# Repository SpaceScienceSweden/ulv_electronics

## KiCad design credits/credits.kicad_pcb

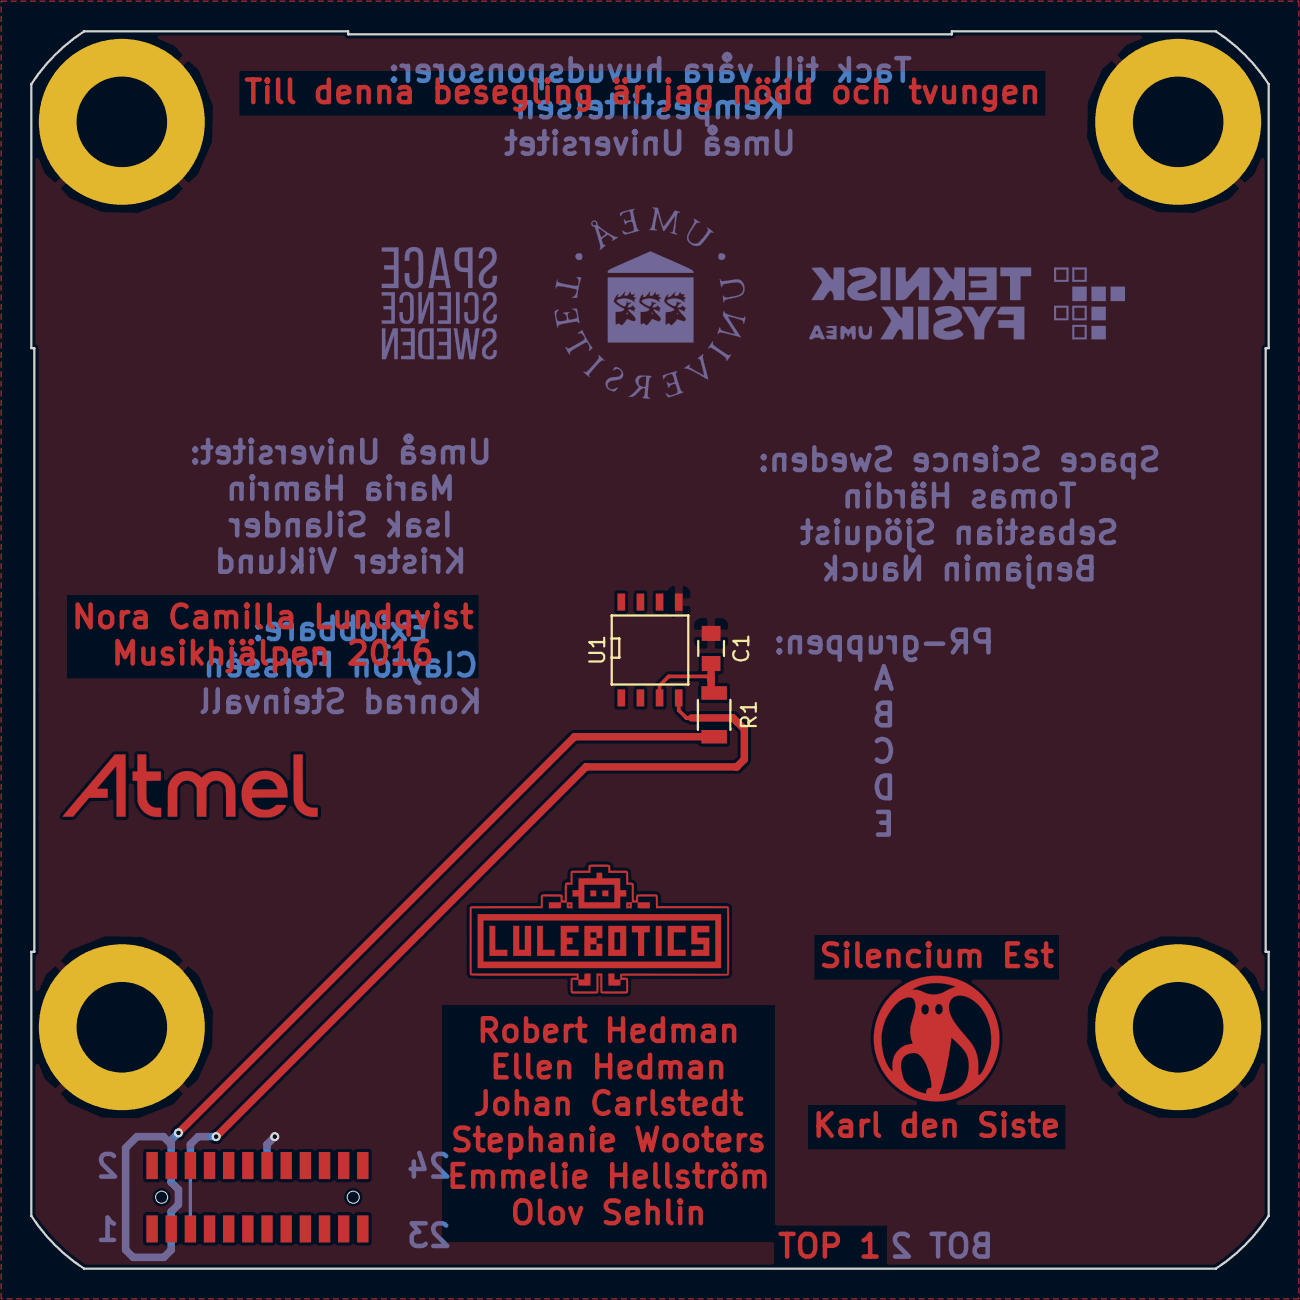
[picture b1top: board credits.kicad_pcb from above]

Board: 2 copper layers, 82.0 x 82.0 mm, 8 parts (1 on the bottom side), 4 nets.

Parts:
C1: 100n; C_0805
P1: CONN_02X12; LPPB122NFSP-RC-backpads-mirrored
P8, P9, P10, P11: M6; M6_PTH
R1: 0; R_1206
U1: DS18B20Z; SOIC-8-N

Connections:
+3V3: P1.3, P1.4, R1.2
/ONEWIRE: P1.5, P1.6, U1.4
GND: C1.2, P1.13, P1.14, P1.15, P1.17, P8.1, P9.1, P10.1, P11.1, U1.5
unnamed: C1.1, R1.1, U1.3

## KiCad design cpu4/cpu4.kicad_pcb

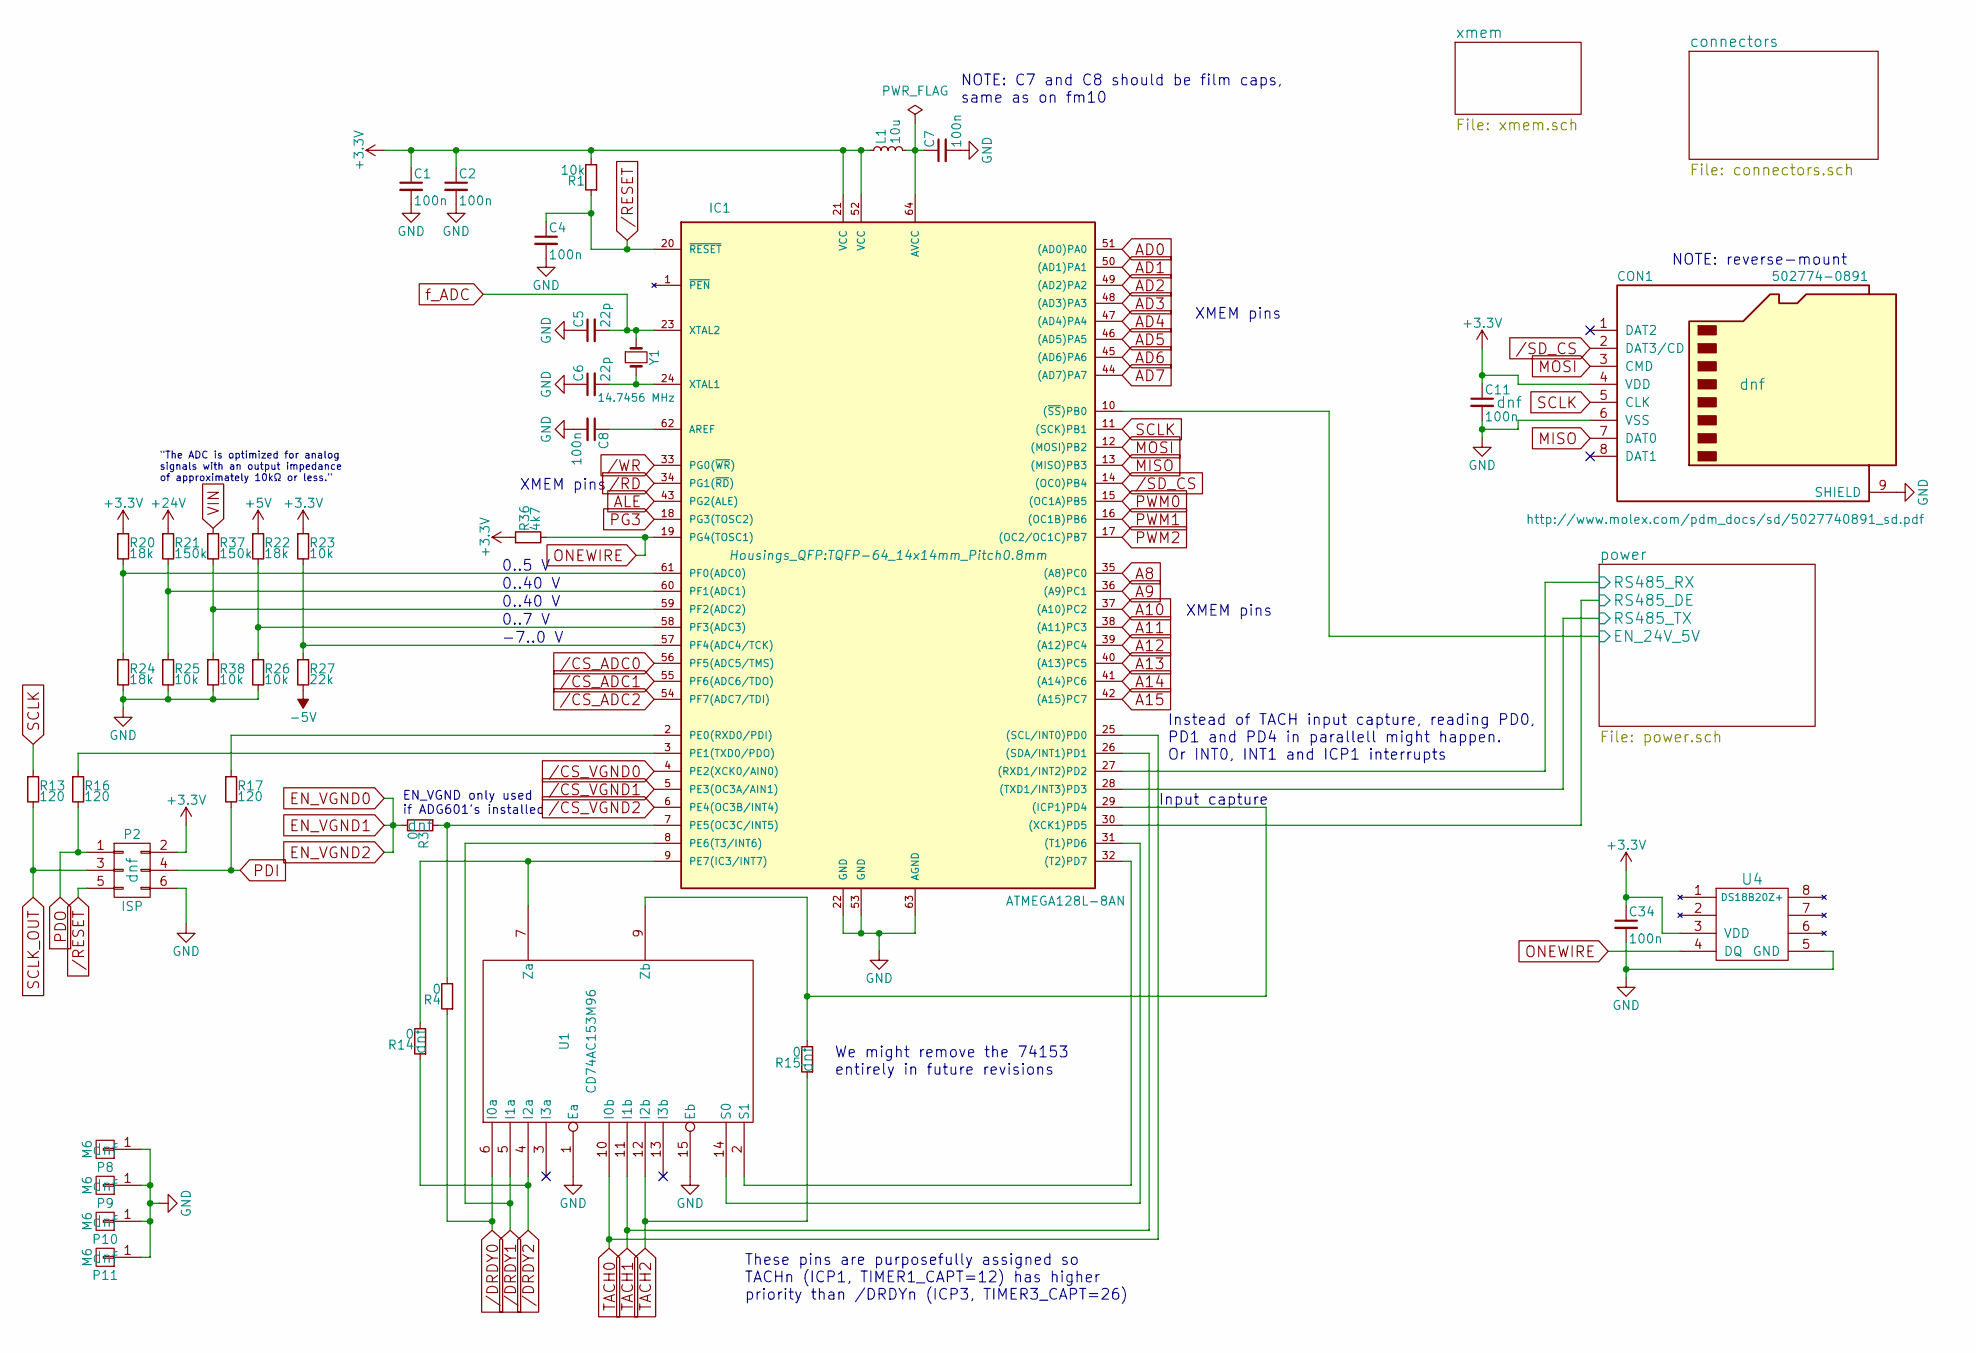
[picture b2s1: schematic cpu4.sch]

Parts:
C1: 100n; C_0805; Mfg. Part Number CGA4J3X7T2E104M125AE; Farnell PN 2211003
C2, C4, C11, C34: 100n; C_0805
C5: 22p; C_0805; Mfg. Part Number C0805X220J5GACTU; Mouser PN 80-C0805X220J5G
C6: 22p; C_0805
C7: 100n; C_1210; Mfg. Part Number ECH-U1C104GX5; Farnell PN 9695001
C8: 100n; C_1210
CON1: 502774-0891; Molex_502774-0891; Mfg. Part Number 502774-0891
IC1: ATMEGA128L-8AN; TQFP-64_14x14mm_Pitch0.8mm; Mfg. Part Number ATmega128L–8AN; Mouser PN 556-ATMEGA128L-8AN
L1: 10u; L_1008; Mfg. Part Number 74479887310A; Mouser PN 710-74479887310A
P2: ISP; Pin_Header_Straight_2x03
P8, P9, P10, P11: M6; M6_PTH
R1, R23, R25, R26, R38: 10k; R_0805
R3, R4, R14, R15: 0; R_1206
R13, R16, R17: 120; R_0805
R20, R22, R24: 18k; R_0805
R21, R37: 150k; R_0805
R27: 22k; R_0805
R36: 4k7; R_0805
U1: CD74AC153M96; SOIC-16_3.9x9.9mm_Pitch1.27mm; Mfg. Part Number CD74AC153M96; Farnell PN 2334932
U4: DS18B20Z+; SOIC-8-N; Mfg. Part Number DS18B20Z+; Farnell PN 2518724
Y1: 14.7456 MHz; Crystal_HC49-SD_SMD; Mfg. Part Number ABLS-14.7456MHZ-K4T; Mouser PN 815-ABLS-14.74MK4-T

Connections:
+3V3: C1.1, C2.1, C11.1, C34.1, CON1.4 (VDD), IC1.21 (VCC), IC1.52 (VCC), L1.1, P2.2, R1.2, R20.1, R23.1, R36.1, U1.16 (VCC), U4.3 (VDD); also elsewhere on the board
+5V: R22.1; also elsewhere on the board
+24V: R21.1; also elsewhere on the board
-5V: R27.2; also elsewhere on the board
/CS_ADC0: IC1.56 (PF5(ADC5/TMS)); also elsewhere on the board
/CS_ADC1: IC1.55 (PF6(ADC6/TDO)); also elsewhere on the board
/CS_ADC2: IC1.54 (PF7(ADC7/TDI)); also elsewhere on the board
/CS_VGND0: IC1.4 (PE2(XCK0/AIN0)); also elsewhere on the board
/CS_VGND1: IC1.5 (PE3(OC3A/AIN1)); also elsewhere on the board
/CS_VGND2: IC1.6 (PE4(OC3B/INT4)); also elsewhere on the board
/DRDY0: R4.1, U1.6 (I0a); also elsewhere on the board
/DRDY1: IC1.8 (PE6(T3/INT6)), U1.5 (I1a); also elsewhere on the board
/DRDY2: R14.1, U1.4 (I2a); also elsewhere on the board
/RD: IC1.34 (PG1(~RD~)); also elsewhere on the board
/RESET: C4.1, IC1.20 (~RESET), P2.5, R1.1; also elsewhere on the board
/SD_CS: CON1.2 (DAT3/CD), IC1.14 ((OC0)PB4)
/WR: IC1.33 (PG0(~WR~)); also elsewhere on the board
/power/EN_24V_5V: IC1.10 ((~SS~)PB0); also elsewhere on the board
/power/RS485_DE: IC1.30 ((XCK1)PD5); also elsewhere on the board
/power/RS485_RX: IC1.27 ((RXD1/INT2)PD2); also elsewhere on the board
/power/RS485_TX: IC1.28 ((TXD1/INT3)PD3); also elsewhere on the board
A8: IC1.35 ((A8)PC0); also elsewhere on the board
A9: IC1.36 ((A9)PC1); also elsewhere on the board
A10: IC1.37 ((A10)PC2); also elsewhere on the board
A11: IC1.38 ((A11)PC3); also elsewhere on the board
A12: IC1.39 ((A12)PC4); also elsewhere on the board
A13: IC1.40 ((A13)PC5); also elsewhere on the board
A14: IC1.41 ((A14)PC6); also elsewhere on the board
A15: IC1.42 ((A15)PC7); also elsewhere on the board
AD0: IC1.51 ((AD0)PA0); also elsewhere on the board
AD1: IC1.50 ((AD1)PA1); also elsewhere on the board
AD2: IC1.49 ((AD2)PA2); also elsewhere on the board
AD3: IC1.48 ((AD3)PA3); also elsewhere on the board
AD4: IC1.47 ((AD4)PA4); also elsewhere on the board
AD5: IC1.46 ((AD5)PA5); also elsewhere on the board
AD6: IC1.45 ((AD6)PA6); also elsewhere on the board
AD7: IC1.44 ((AD7)PA7); also elsewhere on the board
ALE: IC1.43 (PG2(ALE)); also elsewhere on the board
EN_VGND0: R3.2; also elsewhere on the board
GND: C1.2, C2.2, C4.2, C5.1, C6.1, C7.2, C8.2, C11.2, C34.2, CON1.6 (VSS), CON1.9 (SHIELD), IC1.22 (GND), IC1.53 (GND), IC1.63 (AGND), P2.6, P8.1, P9.1, P10.1, P11.1, R24.2, R25.2, R26.2, R38.2, U1.1 (Ea), U1.8 (GND), U1.15 (Eb), U4.5 (GND); also elsewhere on the board
MISO: CON1.7 (DAT0), IC1.13 ((MISO)PB3); also elsewhere on the board
MOSI: CON1.3 (CMD), IC1.12 ((MOSI)PB2); also elsewhere on the board
unnamed: C6.2, IC1.24 (XTAL1), Y1.2
unnamed: C7.1, IC1.64 (AVCC), L1.2
unnamed: C8.1, IC1.62 (AREF)
unnamed: IC1.2 (PE0(RXD0/PDI)), R17.1
unnamed: IC1.3 (PE1(TXD0/PDO)), R16.1
unnamed: IC1.7 (PE5(OC3C/INT5)), R3.1, R4.2
unnamed: IC1.9 (PE7(IC3/INT7)), R14.2, U1.7 (Za)
unnamed: IC1.29 ((ICP1)PD4), R15.2, U1.9 (Zb)
unnamed: IC1.31 ((T1)PD6), U1.14 (S0)
unnamed: IC1.32 ((T2)PD7), U1.2 (S1)
unnamed: IC1.57 (PF4(ADC4/TCK)), R23.2, R27.1
unnamed: IC1.58 (PF3(ADC3)), R22.2, R26.1
unnamed: IC1.59 (PF2(ADC2)), R37.2, R38.1
unnamed: IC1.60 (PF1(ADC1)), R21.2, R25.1
unnamed: IC1.61 (PF0(ADC0)), R20.2, R24.1
ONEWIRE: IC1.19 (PG4(TOSC1)), R36.2, U4.4 (DQ); also elsewhere on the board
PDI: P2.4, R17.2; also elsewhere on the board
PDO: P2.1, R16.2; also elsewhere on the board
PG3: IC1.18 (PG3(TOSC2)); also elsewhere on the board
PWM0: IC1.15 ((OC1A)PB5); also elsewhere on the board
PWM1: IC1.16 ((OC1B)PB6); also elsewhere on the board
PWM2: IC1.17 ((OC2/OC1C)PB7); also elsewhere on the board
SCLK: CON1.5 (CLK), IC1.11 ((SCK)PB1), R13.1; also elsewhere on the board
SCLK_OUT: P2.3, R13.2; also elsewhere on the board
TACH0: IC1.25 ((SCL/INT0)PD0), U1.10 (I0b); also elsewhere on the board
TACH1: IC1.26 ((SDA/INT1)PD1), U1.11 (I1b); also elsewhere on the board
TACH2: R15.1, U1.12 (I2b); also elsewhere on the board
VIN: R37.1; also elsewhere on the board
f_ADC: C5.2, IC1.23 (XTAL2), Y1.1; also elsewhere on the board

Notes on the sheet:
These pins are purposefully assigned so TACHn (ICP1, TIMER1_CAPT=12) has higher priority than /DRDYn (ICP3, TIMER3_CAPT=26)
XMEM pins
Input capture
"The ADC is optimized for analog signals with an output impedance of approximately 10kΩ or less."
0..40 V
0..5 V
0..7 V
-7..0 V
NOTE: reverse-mount
Instead of TACH input capture, reading PD0, PD1 and PD4 in parallell might happen. Or INT0, INT1 and ICP1 interrupts
EN_VGND only used if ADG601's installed
We might remove the 74153 entirely in future revisions
NOTE: C7 and C8 should be film caps, same as on fm10

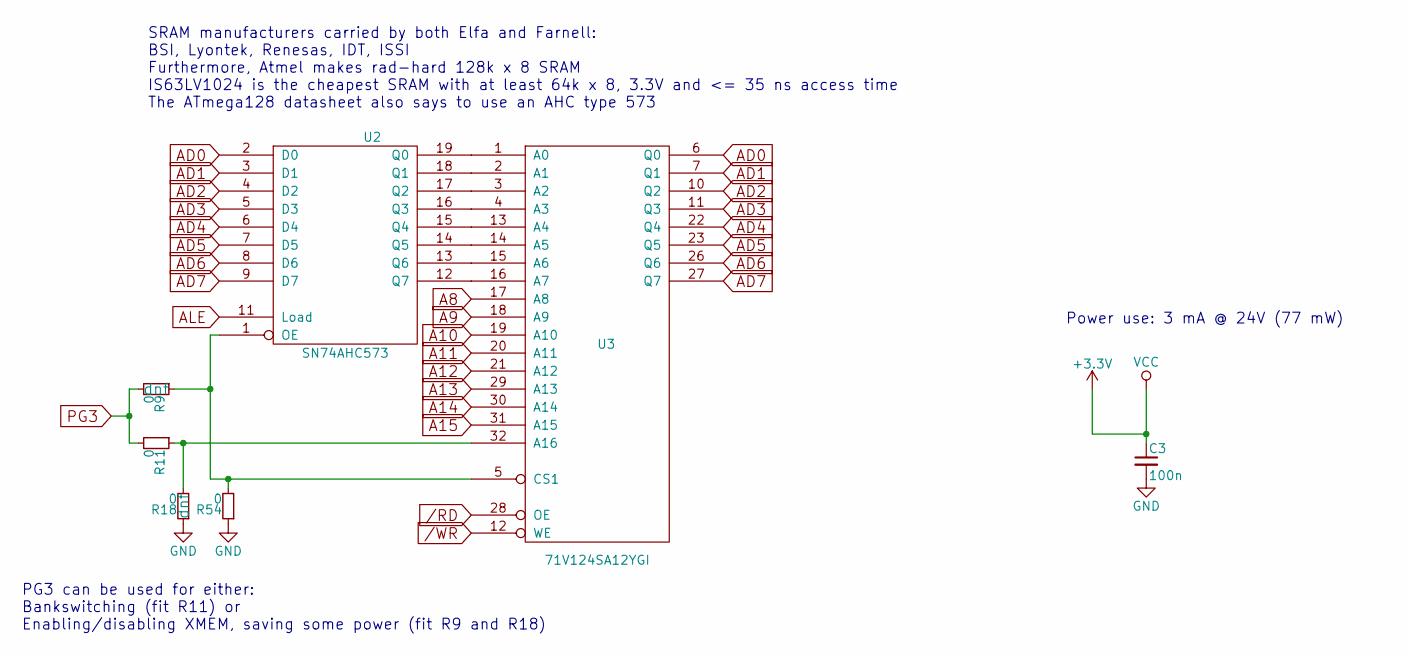
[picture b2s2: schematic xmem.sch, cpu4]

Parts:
C3: 100n; C_0805
R9, R11, R18, R54: 0; R_1206
U2: SN74AHC573; SO-20; Mfg. Part Number SN74AHC573DW; Farnell PN 1287471
U3: 71V124SA12YGI; SOJ-32; Mouser PN 972-71V124SA12YGI

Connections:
+3V3: C3.1, U2.20 (VCC), U3.8 (VCC), U3.24 (VCC); also elsewhere on the board
/RD: U3.28 (OE); also elsewhere on the board
/WR: U3.12 (WE); also elsewhere on the board
A8: U3.17 (A8); also elsewhere on the board
A9: U3.18 (A9); also elsewhere on the board
A10: U3.19 (A10); also elsewhere on the board
A11: U3.20 (A11); also elsewhere on the board
A12: U3.21 (A12); also elsewhere on the board
A13: U3.29 (A13); also elsewhere on the board
A14: U3.30 (A14); also elsewhere on the board
A15: U3.31 (A15); also elsewhere on the board
AD0: U2.2 (D0), U3.6 (Q0); also elsewhere on the board
AD1: U2.3 (D1), U3.7 (Q1); also elsewhere on the board
AD2: U2.4 (D2), U3.10 (Q2); also elsewhere on the board
AD3: U2.5 (D3), U3.11 (Q3); also elsewhere on the board
AD4: U2.6 (D4), U3.22 (Q4); also elsewhere on the board
AD5: U2.7 (D5), U3.23 (Q5); also elsewhere on the board
AD6: U2.8 (D6), U3.26 (Q6); also elsewhere on the board
AD7: U2.9 (D7), U3.27 (Q7); also elsewhere on the board
ALE: U2.11 (Load); also elsewhere on the board
GND: C3.2, R18.1, R54.1, U2.10 (GND), U3.9 (GND), U3.25 (GND); also elsewhere on the board
unnamed: R11.1, R18.2, U3.32 (A16)
unnamed: R9.1, R54.2, U2.1 (OE), U3.5 (CS1)
unnamed: U2.12 (Q7), U3.16 (A7)
unnamed: U2.13 (Q6), U3.15 (A6)
unnamed: U2.14 (Q5), U3.14 (A5)
unnamed: U2.15 (Q4), U3.13 (A4)
unnamed: U2.16 (Q3), U3.4 (A3)
unnamed: U2.17 (Q2), U3.3 (A2)
unnamed: U2.18 (Q1), U3.2 (A1)
unnamed: U2.19 (Q0), U3.1 (A0)
PG3: R9.2, R11.2; also elsewhere on the board

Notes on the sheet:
SRAM manufacturers carried by both Elfa and Farnell: BSI, Lyontek, Renesas, IDT, ISSI Furthermore, Atmel makes rad-hard 128k x 8 SRAM IS63LV1024 is the cheapest SRAM with at least 64k x 8, 3.3V and <= 35 ns access time The ATmega128 datasheet also says to use an AHC type 573
Power use: 3 mA @ 24V (77 mW)
PG3 can be used for either: Bankswitching (fit R11) or Enabling/disabling XMEM, saving some power (fit R9 and R18)

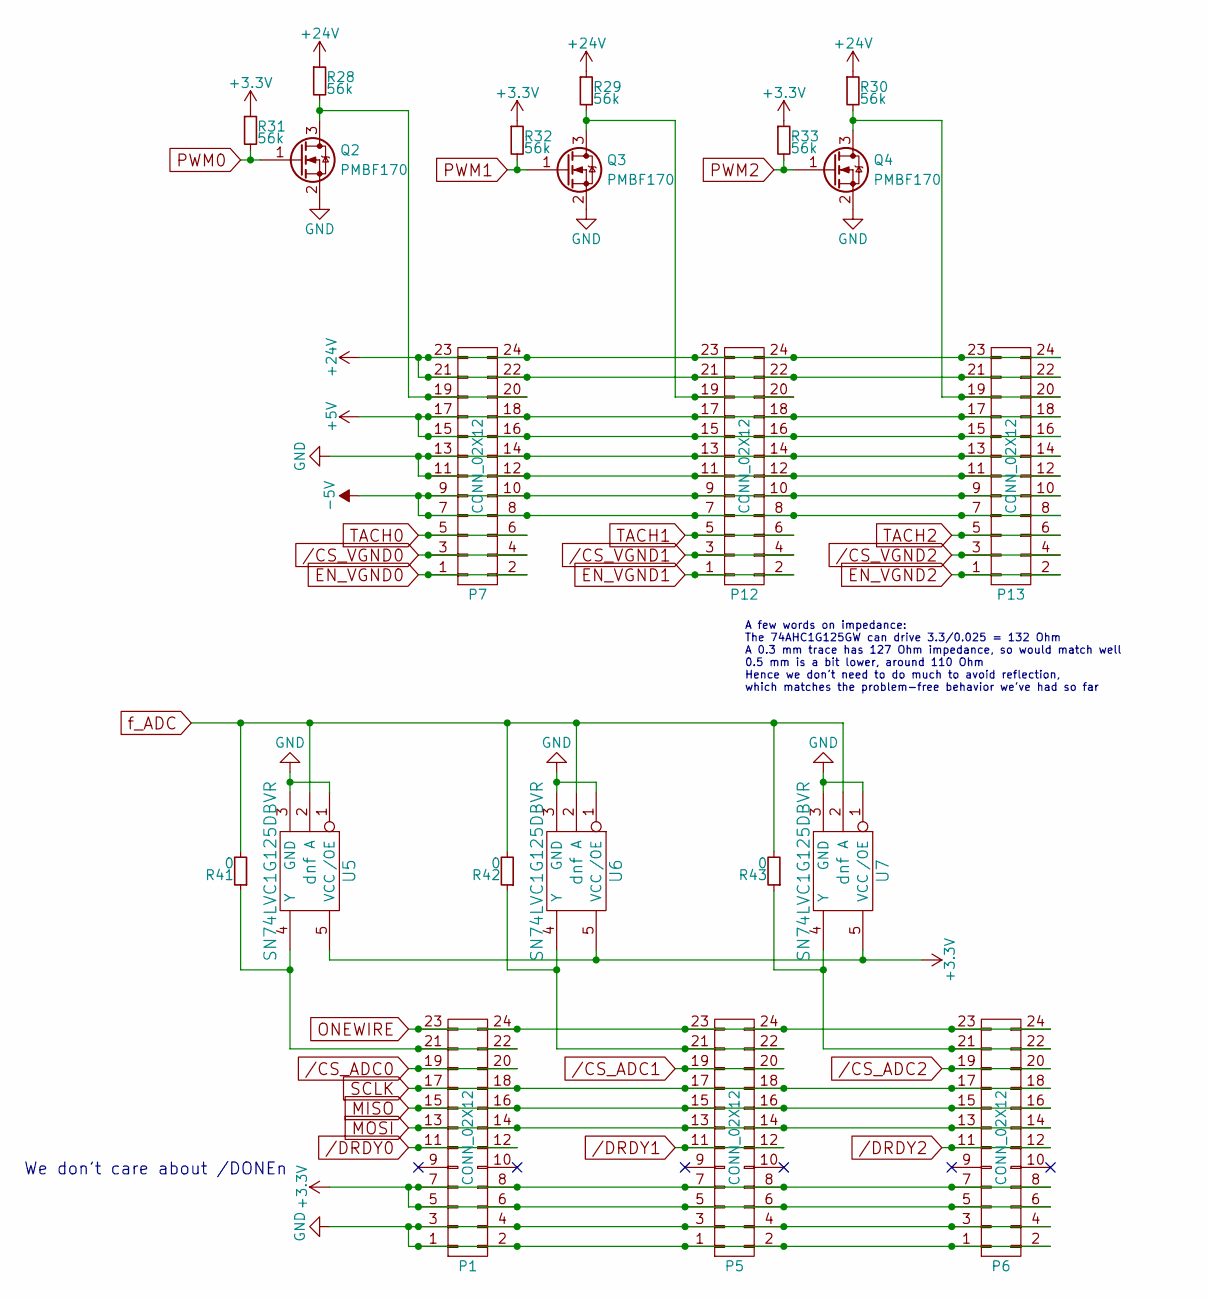
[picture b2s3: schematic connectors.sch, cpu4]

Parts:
P1, P5, P6, P12, P13: CONN_02X12; FTSH-112-04-L-D-RA-3x12; Mfg. Part Number FTSH-112-04-L-D-RA
P7: CONN_02X12; FTSH-112-04-L-D-RA-3x12; Mfg. Part Number FTSH-112-04-L-D-RA; Farnell PN 1767213
Q2: PMBF170; SOT-23; Mfg. Part Number PMBF170,215; Farnell PN 1081473
Q3, Q4: PMBF170; SOT-23
R28, R29, R30, R31, R32, R33: 56k; R_0805
R41, R42, R43: 0; R_1206
U5, U6, U7: SN74LVC1G125DBVR; SOT-23-5

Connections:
+3V3: P1.5, P1.6, P1.7, P1.8, P5.5, P5.6, P5.7, P5.8, P6.5, P6.6, P6.7, P6.8, R31.1, R32.1, R33.1, U5.5 (VCC), U6.5 (VCC), U7.5 (VCC); also elsewhere on the board
+5V: P7.15, P7.16, P7.17, P7.18, P12.15, P12.16, P12.17, P12.18, P13.15, P13.16, P13.17, P13.18; also elsewhere on the board
+24V: P7.21, P7.22, P7.23, P7.24, P12.21, P12.22, P12.23, P12.24, P13.21, P13.22, P13.23, P13.24, R28.1, R29.1, R30.1; also elsewhere on the board
-5V: P7.7, P7.8, P7.9, P7.10, P12.7, P12.8, P12.9, P12.10, P13.7, P13.8, P13.9, P13.10; also elsewhere on the board
/CS_ADC0: P1.19, P1.20; also elsewhere on the board
/CS_ADC1: P5.19, P5.20; also elsewhere on the board
/CS_ADC2: P6.19, P6.20; also elsewhere on the board
/CS_VGND0: P7.3, P7.4; also elsewhere on the board
/CS_VGND1: P12.3, P12.4; also elsewhere on the board
/CS_VGND2: P13.3, P13.4; also elsewhere on the board
/DRDY0: P1.11, P1.12; also elsewhere on the board
/DRDY1: P5.11, P5.12; also elsewhere on the board
/DRDY2: P6.11, P6.12; also elsewhere on the board
EN_VGND0: P7.1, P7.2, P12.1, P12.2, P13.1, P13.2; also elsewhere on the board
GND: P1.1, P1.2, P1.3, P1.4, P5.1, P5.2, P5.3, P5.4, P6.1, P6.2, P6.3, P6.4, P7.11, P7.12, P7.13, P7.14, P12.11, P12.12, P12.13, P12.14, P13.11, P13.12, P13.13, P13.14, Q2.2 (S), Q3.2 (S), Q4.2 (S), U5.1 (/OE), U5.3 (GND), U6.1 (/OE), U6.3 (GND), U7.1 (/OE), U7.3 (GND); also elsewhere on the board
MISO: P1.15, P1.16, P5.15, P5.16, P6.15, P6.16; also elsewhere on the board
MOSI: P1.13, P1.14, P5.13, P5.14, P6.13, P6.14; also elsewhere on the board
unnamed: P1.21, P1.22, R41.1, U5.4 (Y)
unnamed: P5.21, P5.22, R42.1, U6.4 (Y)
unnamed: P6.21, P6.22, R43.1, U7.4 (Y)
unnamed: P7.19, P7.20, Q2.3 (D), R28.2
unnamed: P12.19, P12.20, Q3.3 (D), R29.2
unnamed: P13.19, P13.20, Q4.3 (D), R30.2
ONEWIRE: P1.23, P1.24, P5.23, P5.24, P6.23, P6.24; also elsewhere on the board
PWM0: Q2.1 (G), R31.2; also elsewhere on the board
PWM1: Q3.1 (G), R32.2; also elsewhere on the board
PWM2: Q4.1 (G), R33.2; also elsewhere on the board
SCLK: P1.17, P1.18, P5.17, P5.18, P6.17, P6.18; also elsewhere on the board
TACH0: P7.5, P7.6; also elsewhere on the board
TACH1: P12.5, P12.6; also elsewhere on the board
TACH2: P13.5, P13.6; also elsewhere on the board
f_ADC: R41.2, R42.2, R43.2, U5.2 (A), U6.2 (A), U7.2 (A); also elsewhere on the board

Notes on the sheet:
A few words on impedance: The 74AHC1G125GW can drive 3.3/0.025 = 132 Ohm A 0.3 mm trace has 127 Ohm impedance, so would match well 0.5 mm is a bit lower, around 110 Ohm Hence we don't need to do much to avoid reflection, which matches the problem-free behavior we've had so far
We don't care about /DONEn

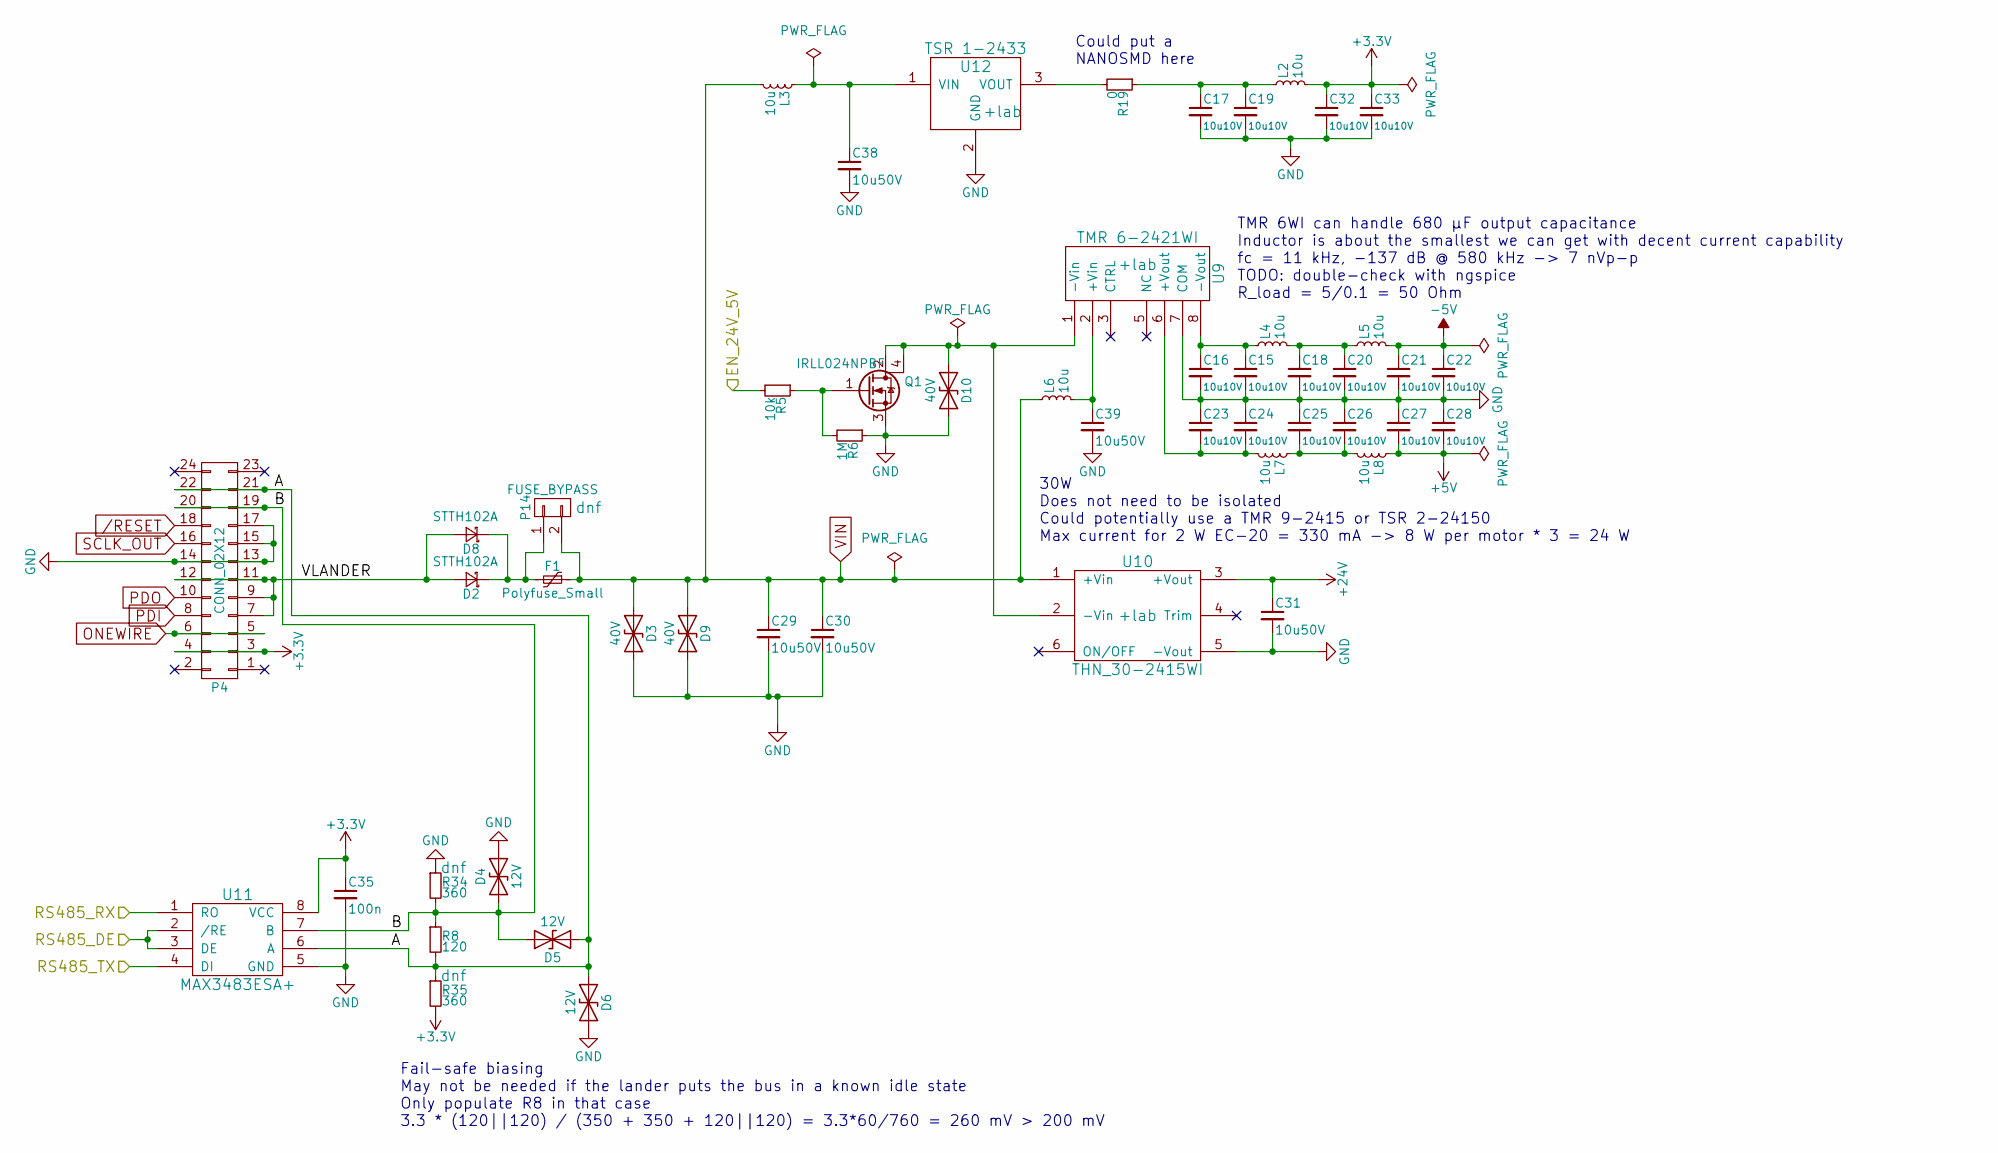
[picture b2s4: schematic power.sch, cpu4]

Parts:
C15: 10u10V; C_1210; Mfg. Part Number C1210X106K8NACAUTO; Mouser PN 80-C1210X106K8NAUTO
C16, C17, C18, C19, C20, C21, C22, C23, C24, C25, C26, C27, C28, C32, C33: 10u10V; C_1210
C29: 10u50V; C_1210; Mfg. Part Number CGA6P3X7S1H106K250AE; Farnell PN 2435524
C30, C31, C38, C39: 10u50V; C_1210
C35: 100n; C_0805
D2: STTH102A; SMA_Standard; Mfg. Part Number STTH102A; Farnell PN 9907874
D3: 40V; SMA_Standard; Mfg. Part Number 824501401; Farnell PN 2536561
D4: 12V; SMA_Standard; Mfg. Part Number 824501121; Farnell PN 2536587
D5, D6: 12V; SMA_Standard
D8: STTH102A; SMA_Standard
D9, D10: 40V; SMA_Standard
F1: Polyfuse_Small; Fuse_SMD2920; Mfg. Part Number 0ZCF0100AF2A; Mouser PN 530-0ZCF0100AF2A
L2, L3, L4, L5, L6, L7, L8: 10u; L_1008
P4: CONN_02X12; LPPB122NFSP-RC; Mfg. Part Number LPPB122NFSP-RC; Digikey PN S9007E-12-ND
P14: FUSE_BYPASS; solder_bridge_1mm
Q1: IRLL024NPBF; SOT-223; Mfg. Part Number IRLL024NPBF; Farnell PN 8651205
R5: 10k; R_0805
R6: 1M; R_0805
R8: 120; R_0805
R19: 0; R_1206
R34, R35: 360; R_0805
U9: TMR 6-2421WI; TMR_6-2421WI; Mfg. Part Number TMR 6-2421WI; Farnell PN 2363824
U10: THN_30-2415WI; THN_30-2415; Mfg. Part Number THN 30-2415WI; Farnell PN 2322198
U11: MAX3483ESA+; SOIC-8_3.9x4.9mm_Pitch1.27mm; Mfg. Part Number MAX3483ESA+; Farnell PN 2519249
U12: TSR 1-2433; TSR_1; Mfg. Part Number TSR 1-2433; Farnell PN 1696319

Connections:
+3V3: C32.1, C33.1, C35.1, L2.2, P4.3, P4.4, R35.2, U11.8 (VCC); also elsewhere on the board
+5V: C27.2, C28.2, L8.1; also elsewhere on the board
+24V: C31.1, U10.3 (+Vout); also elsewhere on the board
-5V: C21.1, C22.1, L5.2; also elsewhere on the board
/RESET: P4.18; also elsewhere on the board
/power/A: D5.1 (A1), D6.1 (A1), P4.21, P4.22, R8.2, R35.1, U11.6 (A)
/power/B: D4.1 (A1), D5.2 (A2), P4.19, P4.20, R8.1, R34.2, U11.7 (B)
/power/EN_24V_5V: R5.2; also elsewhere on the board
/power/RS485_DE: U11.2 (/RE), U11.3 (DE); also elsewhere on the board
/power/RS485_RX: U11.1 (RO); also elsewhere on the board
/power/RS485_TX: U11.4 (DI); also elsewhere on the board
/power/VLANDER: D2.2 (A), D8.2 (A), P4.7, P4.9, P4.11, P4.12
GND: C15.2, C16.2, C17.2, C18.2, C19.2, C20.2, C21.2, C22.2, C23.1, C24.1, C25.1, C26.1, C27.1, C28.1, C29.2, C30.2, C31.2, C32.2, C33.2, C35.2, C38.2, C39.2, D3.2 (A2), D4.2 (A2), D6.2 (A2), D9.2 (A2), D10.2 (A2), P4.13, P4.14, P4.15, P4.17, Q1.3 (S), R6.1, R34.1, U9.7 (COM), U10.5 (-Vout), U11.5 (GND), U12.2 (GND); also elsewhere on the board
unnamed: C15.1, C16.1, L4.1, U9.8 (-Vout)
unnamed: C17.1, C19.1, L2.1, R19.1
unnamed: C18.1, C20.1, L4.2, L5.1
unnamed: C23.2, C24.2, L7.2, U9.6 (+Vout)
unnamed: C25.2, C26.2, L7.1, L8.2
unnamed: C38.1, L3.1, U12.1 (VIN)
unnamed: C39.1, L6.2, U9.2 (+Vin)
unnamed: D2.1 (K), D8.1 (K), F1.2, P14.1
unnamed: D10.1 (A1), Q1.2 (D), Q1.4 (D), U9.1 (-Vin), U10.2 (-Vin)
unnamed: Q1.1 (G), R5.1, R6.2
unnamed: R19.2, U12.3 (VOUT)
ONEWIRE: P4.5, P4.6; also elsewhere on the board
PDI: P4.8; also elsewhere on the board
PDO: P4.10; also elsewhere on the board
SCLK_OUT: P4.16; also elsewhere on the board
VIN: C29.1, C30.1, D3.1 (A1), D9.1 (A1), F1.1, L3.2, L6.1, P14.2, U10.1 (+Vin); also elsewhere on the board

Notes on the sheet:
30W Does not need to be isolated Could potentially use a TMR 9-2415 or TSR 2-24150 Max current for 2 W EC-20 = 330 mA -> 8 W per motor * 3 = 24 W
TMR 6WI can handle 680 µF output capacitance Inductor is about the smallest we can get with decent current capability fc = 11 kHz, -137 dB @ 580 kHz -> 7 nVp-p TODO: double-check with ngspice R_load = 5/0.1 = 50 Ohm
Fail-safe biasing May not be needed if the lander puts the bus in a known idle state Only populate R8 in that case 3.3 * (120||120) / (350 + 350 + 120||120) = 3.3*60/760 = 260 mV > 200 mV
Could put a NANOSMD here

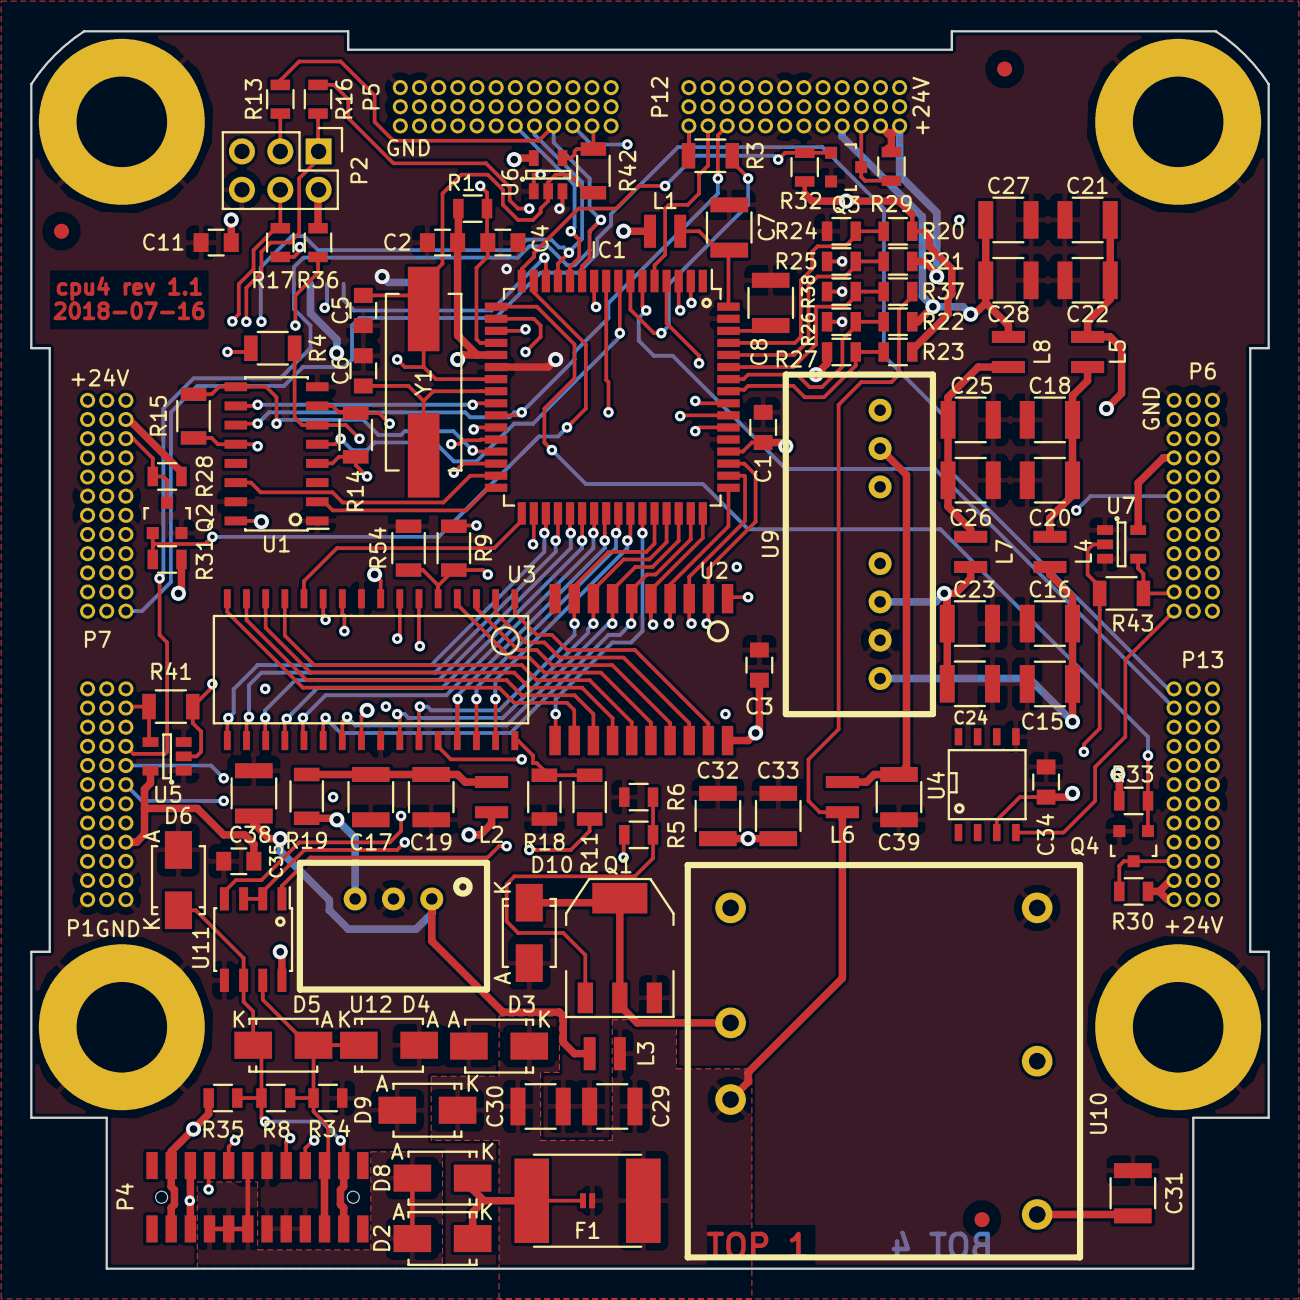
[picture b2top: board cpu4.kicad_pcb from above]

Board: 4 copper layers, 82.0 x 82.0 mm, 121 parts (1 on the bottom side), 101 nets.

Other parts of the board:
REF1, REF2, REF3: Fiducial_1mm_Dia_2.54mm_Outer_CopperTop; Fiducial_1mm_Dia_2.54mm_Outer_CopperTop-paste
